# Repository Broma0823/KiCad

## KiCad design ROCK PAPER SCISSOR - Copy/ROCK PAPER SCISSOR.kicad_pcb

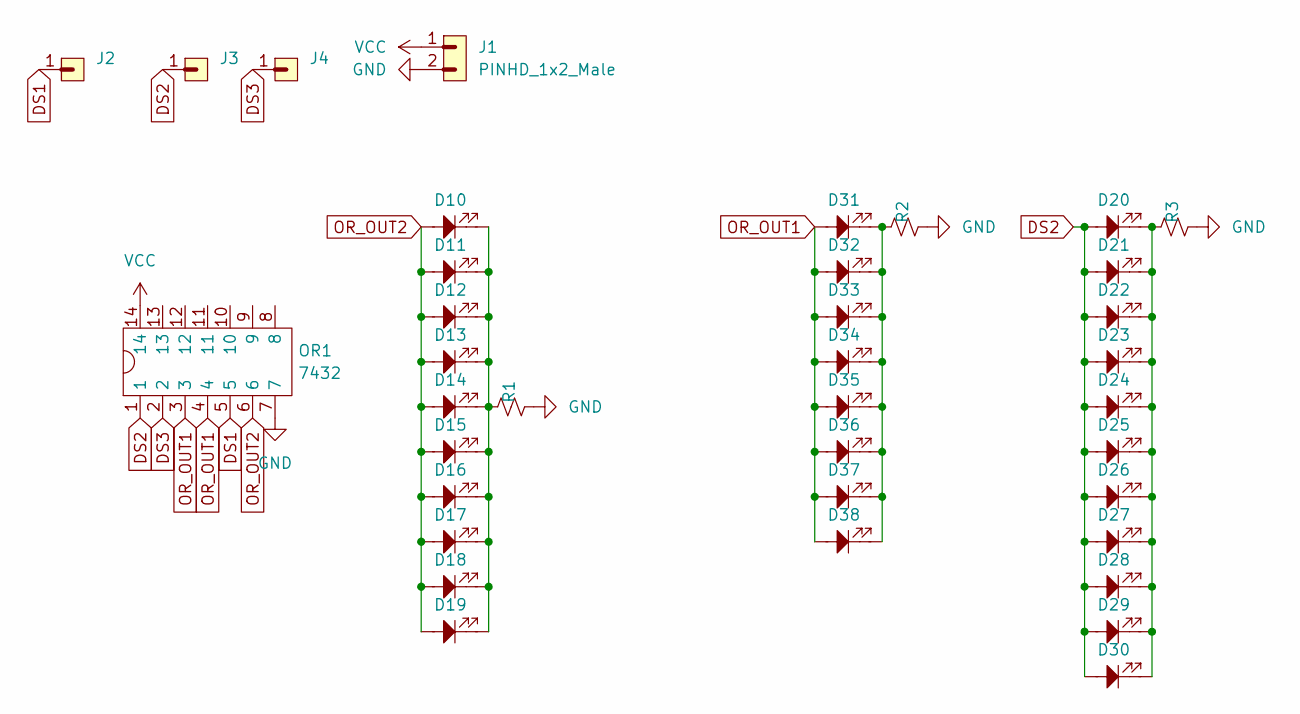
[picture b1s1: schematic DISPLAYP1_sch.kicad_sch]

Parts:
D10, D11, D12, D13, D14, D15, D16, D17, D18, D19, D20, D21, D22, D23, D24, D25, D26, D27, D28, D29, D30, D31, D32, D33, D34, D35, D36, D37, D38: PLAYER2_WIN; LED_D5.0mm
J1: PINHD_1x2_Male; PinHeader_1x02_P2.54mm_Vertical
J2, J3, J4: PINHD_1x1_Male; PinHeader_1x01_P2.54mm_Vertical
OR1: 7432; DIP-14_W7.62mm_LongPads
R1, R2, R3: R_Small_US; R_Axial_DIN0207_L6.3mm_D2.5mm_P7.62mm_Horizontal

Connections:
DS1: J2.1, OR1.5
DS2: D20.2, D21.2, D22.2, D23.2, D24.2, D25.2, D26.2, D27.2, D28.2, D29.2, D30.2, J3.1, OR1.1
DS3: J4.1, OR1.2
GND: J1.2, OR1.7, R1.1, R2.1, R3.1
unnamed: D10.1, D11.1, D12.1, D13.1, D14.1, D15.1, D16.1, D17.1, D18.1, D19.1, R1.2
unnamed: D20.1, D21.1, D22.1, D23.1, D24.1, D25.1, D26.1, D27.1, D28.1, D29.1, D30.1, R3.2
unnamed: D31.1, D32.1, D33.1, D34.1, D35.1, D36.1, D37.1, D38.1, R2.2
OR_OUT1: D31.2, D32.2, D33.2, D34.2, D35.2, D36.2, D37.2, D38.2, OR1.3, OR1.4
OR_OUT2: D10.2, D11.2, D12.2, D13.2, D14.2, D15.2, D16.2, D17.2, D18.2, D19.2, OR1.6
VCC: J1.1, OR1.14

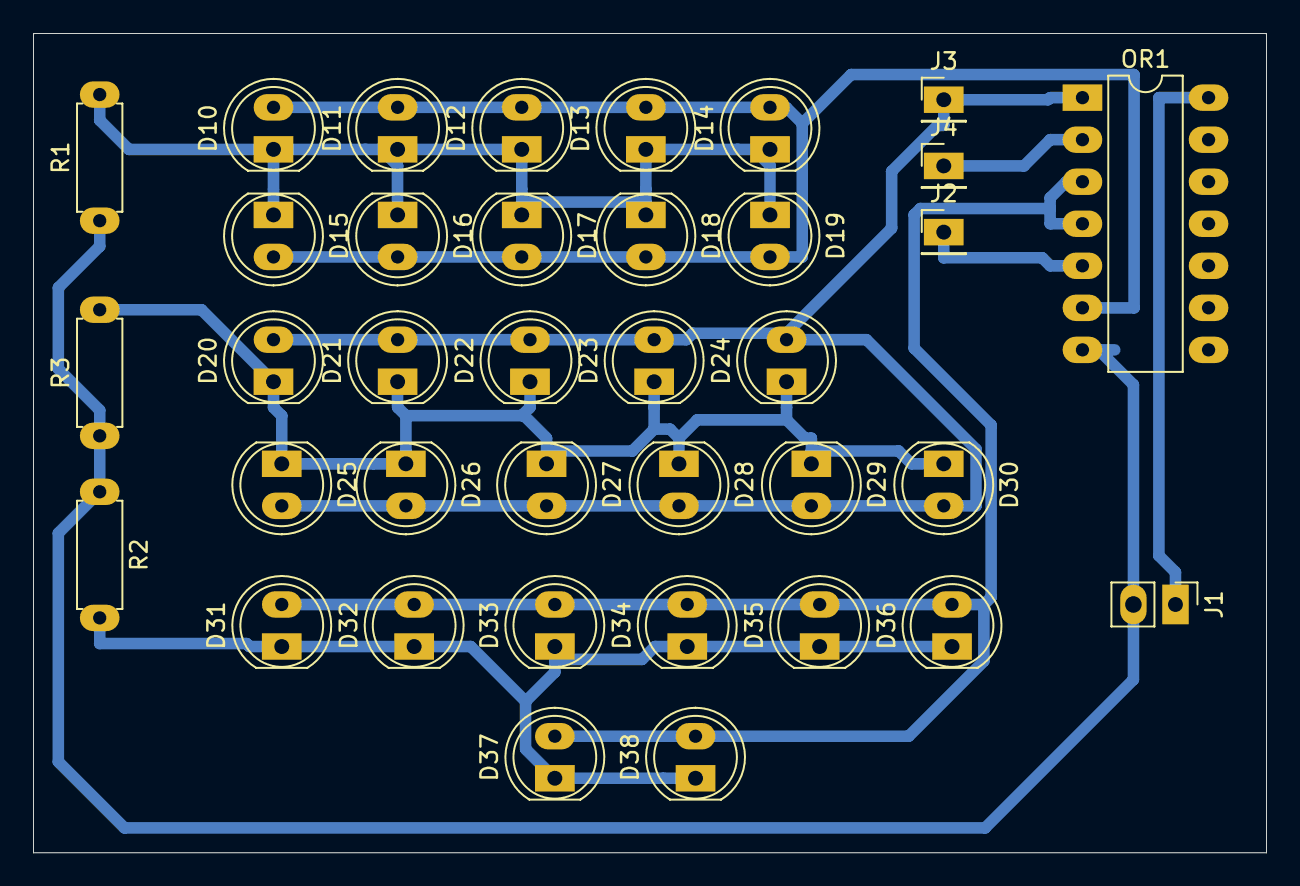
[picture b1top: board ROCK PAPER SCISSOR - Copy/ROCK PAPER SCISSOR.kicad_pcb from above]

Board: 2 copper layers, 74.5 x 49.5 mm, 37 parts (0 on the bottom side), 10 nets.

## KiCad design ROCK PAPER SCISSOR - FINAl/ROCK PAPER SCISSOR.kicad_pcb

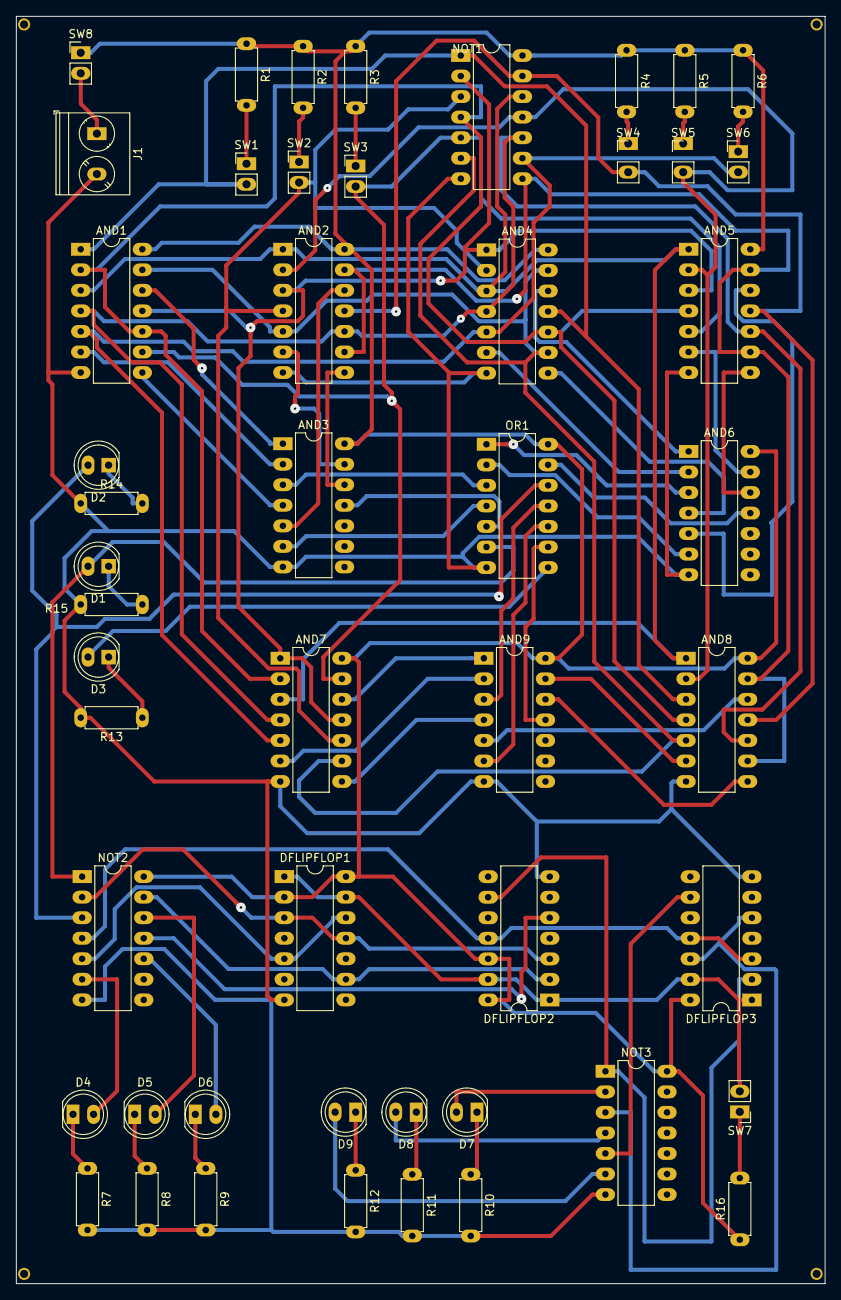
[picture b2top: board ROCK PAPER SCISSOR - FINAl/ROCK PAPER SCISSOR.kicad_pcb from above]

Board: 2 copper layers, 100.0 x 156.7 mm, 50 parts (0 on the bottom side), 76 nets.

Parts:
AND1, AND2, AND4, AND5, AND7, AND8: 7411; DIP-14_W7.62mm_LongPads
AND3, AND6, AND9: 7408; DIP-14_W7.62mm_LongPads
D1: PLAYER1_WIN; LED_D5.0mm
D2: PLAYER2_WIN; LED_D5.0mm
D3: TIE; LED_D5.0mm
D4: PLAYER2_LIFE1; LED_D5.0mm
D5: PLAYER2_LIFE2; LED_D5.0mm
D6: PLAYER2_LIFE3; LED_D5.0mm
D7: PLAYER1_LIFE1; LED_D5.0mm
D8: PLAYER1_LIFE2; LED_D5.0mm
D9: PLAYER1_LIFE3; LED_D5.0mm
DFLIPFLOP1, DFLIPFLOP2, DFLIPFLOP3: 7474; DIP-14_W7.62mm_LongPads
J1: Screw_Terminal_2_P5.00mm; TerminalBlock_Phoenix_PT-1,5-2-5.0-H_1x02_P5.00mm_Horizontal
NOT1, NOT2, NOT3: 7404; DIP-14_W7.62mm_LongPads
OR1: 4075; DIP-14_W7.62mm_LongPads
R1, R2, R3, R4, R5, R6, R7, R8, R9, R10, R11, R12, R13, R14, R15, R16: R_Small_US; R_Axial_DIN0207_L6.3mm_D2.5mm_P7.62mm_Horizontal
SW1, SW2, SW3, SW4, SW5, SW6, SW7: SW_Push; PinHeader_1x02_P2.54mm_Vertical
SW8: SW_SPST; PinHeader_1x02_P2.54mm_Vertical

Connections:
AND3OUT_1: AND3.3, OR1.3
AND3OUT_2: AND3.6, OR1.4
AND3OUT_3: AND3.11, OR1.5
AND6OUT_1: AND6.3, OR1.1
AND6OUT_2: AND6.6, OR1.2
AND6OUT_3: AND6.11, OR1.13
AND9OUT_1: AND9.3, OR1.11
AND9OUT_2: AND9.6, OR1.10
AND9OUT_3: AND9.11, OR1.9
GND: AND1.7, AND2.7, AND3.7, AND4.7, AND5.7, AND6.7, AND7.7, AND8.7, AND9.7, DFLIPFLOP1.7, DFLIPFLOP2.7, DFLIPFLOP3.7, J1.2, NOT1.7, NOT2.7, NOT3.7, OR1.7, R7.2, R8.2, R9.2, R10.2, R11.2, R12.2, R13.2, R14.1, R15.1
unnamed: D1.1, R15.2
unnamed: D2.1, R14.2
unnamed: D3.1, R13.1
unnamed: D4.1, R7.1
unnamed: D5.1, R8.1
unnamed: D6.1, R9.1
unnamed: D7.1, R10.1
unnamed: D8.1, R11.1
unnamed: D9.1, R12.1
unnamed: R1.2, SW1.1
unnamed: R2.2, SW2.1
unnamed: R3.2, SW3.1
unnamed: R4.2, SW4.1
unnamed: R5.2, SW5.1
unnamed: R6.2, SW6.1
unnamed: R16.2, SW7.1
unnamed: J1.1, SW8.2 (B)
OR1OUT_1: D2.2, NOT2.3, OR1.12
OR1OUT_2: D1.2, NOT2.1, OR1.6
OR1OUT_3: D3.2, OR1.8
OUT_1': DFLIPFLOP2.11, DFLIPFLOP3.3, DFLIPFLOP3.11, NOT2.4
OUT_2': DFLIPFLOP1.3, DFLIPFLOP1.11, DFLIPFLOP2.3, NOT2.2
P1: AND2.4, AND4.2, AND7.10, NOT1.3, SW2.2
P1': AND1.2, AND1.10, AND4.10, AND5.4, AND7.2, AND8.4, NOT1.4
P1(1)OUT: AND1.12, AND3.1
P1(2)OUT: AND1.6, AND3.2
P1(3)OUT: AND1.8, AND3.4
P1(4)OUT: AND2.12, AND3.5
P1(5)OUT: AND2.6, AND3.13
P1(6)OUT: AND2.8, AND3.12
P2: AND2.2, AND5.2, AND8.2, NOT1.11, SW5.2
P2': AND1.4, AND2.10, AND4.4, AND5.10, AND7.4, AND8.10, NOT1.10
P2(1)OUT: AND4.12, AND6.1
P2(2)OUT: AND4.6, AND6.2
P2(3)OUT: AND4.8, AND6.4
P2(4)OUT: AND5.12, AND6.5
P2(5)OUT: AND5.6, AND6.13
P2(6)OUT: AND5.8, AND6.12
Q1: DFLIPFLOP1.5, DFLIPFLOP1.12, NOT2.5
Q1': D4.2, NOT2.6
Q2: DFLIPFLOP1.9, DFLIPFLOP2.2, NOT2.13
Q2': D5.2, NOT2.12
Q3: DFLIPFLOP2.5, NOT2.11
Q3': D6.2, NOT2.10
Q4: DFLIPFLOP2.9, DFLIPFLOP3.2, NOT3.1
Q4': D7.2, NOT3.2
Q5: DFLIPFLOP3.5, DFLIPFLOP3.12, NOT3.3
Q5': D8.2, NOT3.4
Q6: DFLIPFLOP3.9, NOT3.5
Q6': D9.2, NOT3.6
R1: AND1.1, AND4.11, AND8.3, NOT1.1, SW1.2
R1': AND1.11, AND2.3, AND4.1, AND5.3, AND7.1, AND7.11, NOT1.2
R2: AND2.11, AND5.11, AND8.11, NOT1.13, SW4.2
R2': AND1.3, AND2.1, AND4.3, AND5.1, AND7.3, AND8.1, NOT1.12
RST: DFLIPFLOP1.1, DFLIPFLOP1.13, DFLIPFLOP2.1, DFLIPFLOP2.13, DFLIPFLOP3.1, DFLIPFLOP3.13, SW7.2
S1: AND1.9, AND5.5, AND7.13, NOT1.5, SW3.2
S1': AND1.13, AND2.5, AND4.9, AND4.13, AND7.9, AND8.5, NOT1.6
S2: AND1.5, AND4.5, AND7.5, NOT1.9, SW6.2
S2': AND2.9, AND2.13, AND5.9, AND5.13, AND8.9, AND8.13, NOT1.8
T(1)OUT: AND7.12, AND9.1
T(2)OUT: AND7.6, AND9.2
T(3)OUT: AND7.8, AND9.4
T(4)OUT: AND8.12, AND9.5
T(5)OUT: AND8.6, AND9.13
T(6)OUT: AND8.8, AND9.12
VCC: AND1.14, AND2.14, AND3.14, AND4.14, AND5.14, AND6.14, AND7.14, AND8.14, AND9.14, DFLIPFLOP1.2, DFLIPFLOP1.14, DFLIPFLOP2.12, DFLIPFLOP2.14, DFLIPFLOP3.14, NOT1.14, NOT2.14, NOT3.14, OR1.14, R1.1, R2.1, R3.1, R4.1, R5.1, R6.1, R16.1, SW8.1 (A)

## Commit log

2024-12-12 Create asd
